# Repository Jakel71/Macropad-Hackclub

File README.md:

# Macropad-Hackclub
This is an Macro pad with 16 Buttons with background lighting. Its meant for simplicity and an everyday use. This is the reason why it will have shortcuts for Windows 11. You could adjust the Container of the PCB so that the lights are looking out, but scince I never saw this kind of LED I don't know how big the hole has to be.

In this picture you can see the Box in gray and the PCB in Green.

Here you can see the shematics of th PCB. It could happen that the Analog pins won't allow Digitalinput, then you schould switsh to an other microcontroller (arduino/ESP) with more pins.

Here you can see the PCB and all the components which you have to mount on it. The dimensions are 137x84.5mm this is more than the limit of 100mm in one dimension, but it would become very messy when you would pack it closer together.

You can see here all the parts you need for the case just screew 4 screews in it and its ready to go.

BOM: (list of materials)
- 1 PCB
- 1 Case ( bittom + top part)
- M3x16mm screws
- M3x5mx4mm heatset inserts
- 16 Cherry MX 1 Keyboardbuttons
- 16 Keycaps
- 16 SK6812 MINI-E LEDs
- 1 Seeed XIAO RP2040

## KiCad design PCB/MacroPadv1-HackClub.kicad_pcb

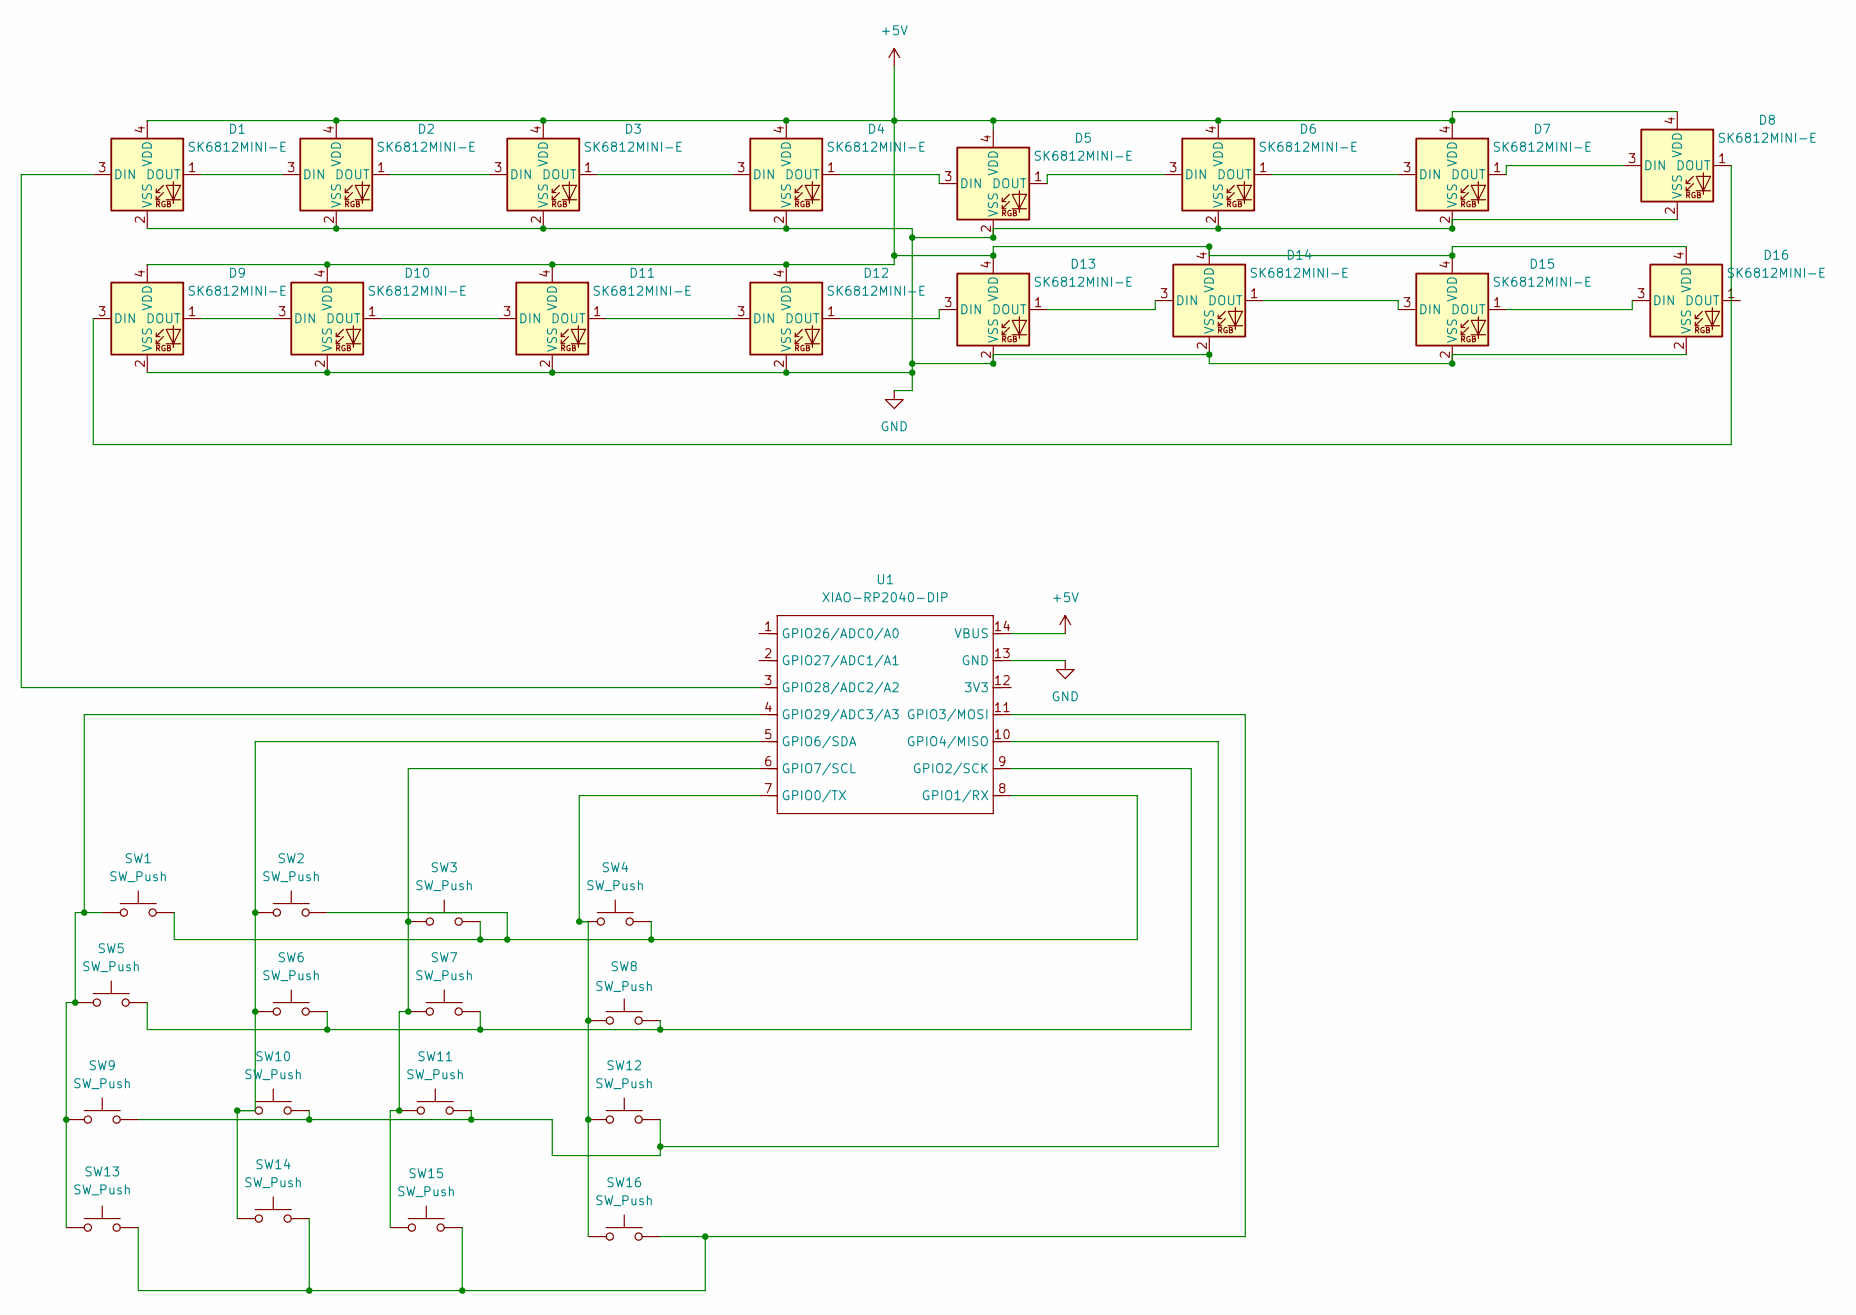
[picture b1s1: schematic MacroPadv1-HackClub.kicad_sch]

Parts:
D1, D2, D3, D4, D5, D6, D7, D8, D9, D10, D11, D12, D13, D14, D15, D16: SK6812MINI-E; MX_SK6812MINI-E
SW1, SW2, SW3, SW4, SW5, SW6, SW7, SW8, SW9, SW10, SW11, SW12, SW13, SW14, SW15, SW16: SW_Push; SW_Cherry_MX_1.00u_PCB
U1: XIAO-RP2040-DIP

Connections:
+5V: D1.4 (VDD), D2.4 (VDD), D3.4 (VDD), D4.4 (VDD), D5.4 (VDD), D6.4 (VDD), D7.4 (VDD), D8.4 (VDD), D9.4 (VDD), D10.4 (VDD), D11.4 (VDD), D12.4 (VDD), D13.4 (VDD), D14.4 (VDD), D15.4 (VDD), D16.4 (VDD), U1.14 (VBUS)
GND: D1.2 (VSS), D2.2 (VSS), D3.2 (VSS), D4.2 (VSS), D5.2 (VSS), D6.2 (VSS), D7.2 (VSS), D8.2 (VSS), D9.2 (VSS), D10.2 (VSS), D11.2 (VSS), D12.2 (VSS), D13.2 (VSS), D14.2 (VSS), D15.2 (VSS), D16.2 (VSS), U1.13 (GND)
unnamed: D1.3 (DIN), U1.3 (GPIO28/ADC2/A2)
unnamed: D1.1 (DOUT), D2.3 (DIN)
unnamed: D2.1 (DOUT), D3.3 (DIN)
unnamed: D3.1 (DOUT), D4.3 (DIN)
unnamed: D4.1 (DOUT), D5.3 (DIN)
unnamed: D5.1 (DOUT), D6.3 (DIN)
unnamed: D6.1 (DOUT), D7.3 (DIN)
unnamed: D7.1 (DOUT), D8.3 (DIN)
unnamed: D8.1 (DOUT), D9.3 (DIN)
unnamed: D9.1 (DOUT), D10.3 (DIN)
unnamed: D10.1 (DOUT), D11.3 (DIN)
unnamed: D11.1 (DOUT), D12.3 (DIN)
unnamed: D12.1 (DOUT), D13.3 (DIN)
unnamed: D13.1 (DOUT), D14.3 (DIN)
unnamed: D14.1 (DOUT), D15.3 (DIN)
unnamed: D15.1 (DOUT), D16.3 (DIN)
unnamed: SW4.1, SW8.1, SW12.1, SW16.1, U1.7 (GPIO0/TX)
unnamed: SW1.2, SW2.2, SW3.2, SW4.2, U1.8 (GPIO1/RX)
unnamed: SW5.2, SW6.2, SW7.2, SW8.2, U1.9 (GPIO2/SCK)
unnamed: SW13.2, SW14.2, SW15.2, SW16.2, U1.11 (GPIO3/MOSI)
unnamed: SW9.2, SW10.2, SW11.2, SW12.2, U1.10 (GPIO4/MISO)
unnamed: SW2.1, SW6.1, SW10.1, SW14.1, U1.5 (GPIO6/SDA)
unnamed: SW3.1, SW7.1, SW11.1, SW15.1, U1.6 (GPIO7/SCL)
unnamed: SW1.1, SW5.1, SW9.1, SW13.1, U1.4 (GPIO29/ADC3/A3)

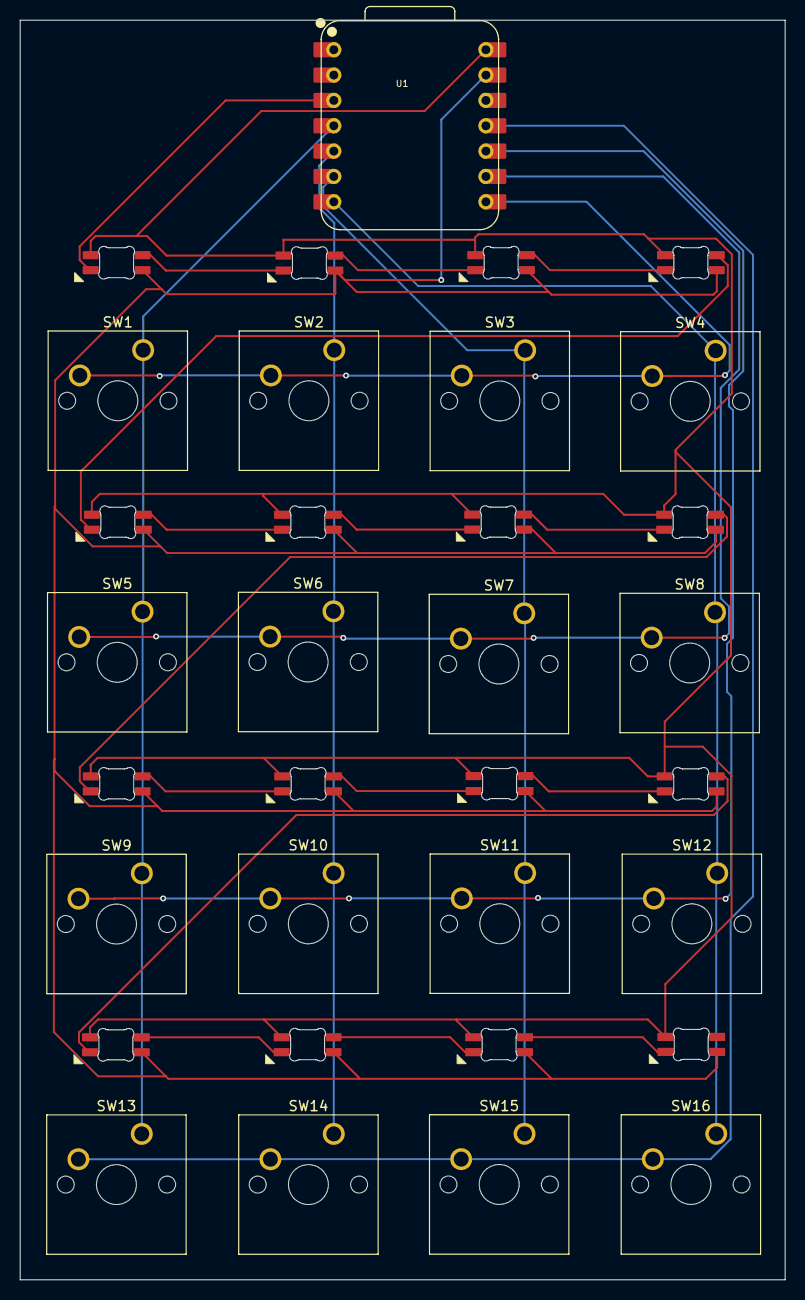
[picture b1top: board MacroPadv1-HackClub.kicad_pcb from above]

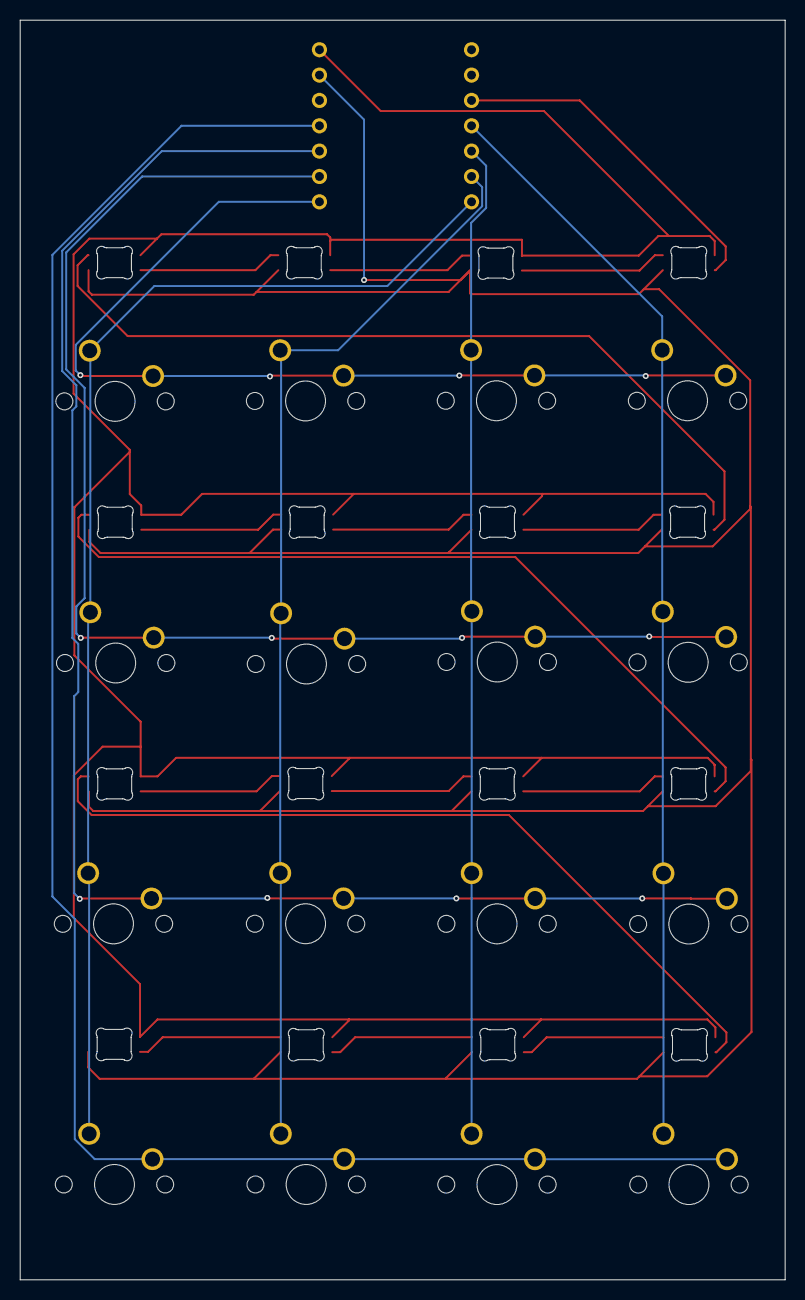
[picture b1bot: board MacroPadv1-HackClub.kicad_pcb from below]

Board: 2 copper layers, 76.6 x 126.2 mm, 33 parts (16 on the bottom side), 26 nets.

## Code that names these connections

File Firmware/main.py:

import board
import digitalio
import time
import usb_hid
from adafruit_hid.keyboard import Keyboard
from adafruit_hid.keycode import Keycode
from adafruit_hid.consumer_control import ConsumerControl
from adafruit_hid.consumer_control_code import ConsumerControlCode
from adafruit_hid.keyboard_layout_us import KeyboardLayoutUS

import neopixel


# -----------------------
# KEYBOARD SETUP
# -----------------------
kbd = Keyboard(usb_hid.devices)
cc = ConsumerControl(usb_hid.devices)
layout = KeyboardLayoutUS(kbd)

# -----------------------
# RGB LED SETUP (16x SK6812 Mini on A2/GPIO28)
# -----------------------
pixel = neopixel.NeoPixel(board.A2, 16, brightness=0.2, auto_write=False)

# All LEDS are red = not ready
for i in range(16):
    pixel[i] = (255, 0, 0)
pixel.show()

# -----------------------
# MATRIX SETUP (4x4)
# -----------------------
# 
# ROWS (right side, Pins 8-11):
#   Pin 8  = GPIO1/RX    = board.RX  oder board.D1
#   Pin 9  = GPIO2/SCK   = board.SCK oder board.D2  
#   Pin 10 = GPIO4/MISO  = board.MISO oder board.D4
#   Pin 11 = GPIO3/MOSI  = board.MOSI oder board.D3
#
# COLUMNS (left side, Pins 4-7):
#   Pin 7 = GPIO0/TX   = board.TX  oder board.D0
#   Pin 6 = GPIO7/SCL  = board.SCL oder board.D7
#   Pin 5 = GPIO6/SDA  = board.SDA oder board.D6
#   Pin 4 = GPIO29/A3  = board.A3
#
# LEDs are on A2 (Pin 3)

row_pins = [board.RX, board.SCK, board.MISO, board.MOSI]  # Pins 8,9,10,11
col_pins = [board.A3, board.SDA, board.SCL, board.TX]     # Pins 4,5,6,7

# Setup Rows as Output (HIGH = deactivated)
rows = []
for pin in row_pins:
    row = digitalio.DigitalInOut(pin)
    row.direction = digitalio.Direction.OUTPUT
    row.value = True  # HIGH = inaktiv
    rows.append(row)

# Setup Columns as Input with Pull-Up
cols = []
for pin in col_pins:
    col = digitalio.DigitalInOut(pin)
    col.direction = digitalio.Direction.INPUT
    col.pull = digitalio.Pull.UP
    cols.append(col)

# -----------------------
# MACRO FUNKTIONS
# -----------------------
def send_macro(keys, modifiers=[]):
    """Sendet eine Tastenkombination"""
    for mod in modifiers:
        kbd.press(mod)
    time.sleep(0.01)
    
    for key in keys:
        kbd.press(key)
        time.sleep(0.01)
        kbd.release(key)
        time.sleep(0.01)
    
    for mod in modifiers:
        kbd.release(mod)

# -----------------------
# KEYMAP DEFINITION
# -----------------------
def key_0():  # Taste 1 // Rickroll
    send_macro([Keycode.R], [Keycode.GUI])  # WIN+R
    time.sleep(0.1)
    layout.write('cmd\n')
    time.sleep(1)
    layout.write('curl ASCII.live&can/zou/hear/me\n')

def key_1():  # Taste 2
    send_macro([Keycode.L], [Keycode.GUI])  # WIN+L // lock screen

def key_2():  # Taste 3
    send_macro([Keycode.F4], [Keycode.ALT])  # ALT+F4 //end current window

def key_3():  # Taste 4
    send_macro([Keycode.D], [Keycode.GUI])  # WIN+D // show desktop

def key_4():  # Taste 5
    send_macro([Keycode.TAB], [Keycode.ALT])  # ALT+TAB // switch window

def key_5():  # Taste 6
    send_macro([Keycode.P], [Keycode.GUI])  # WIN+P // monitor settings

def key_6():  # Taste 7
    send_macro([Keycode.E], [Keycode.GUI])  # WIN+E // open file explorer

def key_7():  # Taste 8
    send_macro([Keycode.LEFT_SHIFT],[Keycode.LEFT_CONTROL], [Keycode.ESCAPE])  # open Taskmanager with STRG+SHIFT+ESC

def key_8():  # Taste 9
    send_macro([Keycode.S], [Keycode.GUI, Keycode.SHIFT])  # WIN+SHIFT+S // Screenshot

def key_9():  # Taste 10
    send_macro([Keycode.I], [Keycode.GUI])  # WIN+I // open settings

def key_10():  # Taste 11
    send_macro([Keycode.K], [Keycode.GUI])  # WIN+K // open connect menu for wireless displays

def key_11():  # Taste 12
    send_macro([Keycode.R], [Keycode.GUI])  # WIN+R // open run dialog

def key_12():  # Taste 13 - Media Play/Pause
    cc.send(ConsumerControlCode.PLAY_PAUSE)

def key_13():  # Taste 14 - Mute
    cc.send(ConsumerControlCode.MUTE)

def key_14():  # Taste 15 - Volume Down
    cc.send(ConsumerControlCode.VOLUME_DECREMENT)

def key_15():  # Taste 16 - Volume Up
    cc.send(ConsumerControlCode.VOLUME_INCREMENT)

# Keymap Array
keymap = [
    [key_0,  key_1,  key_2,  key_3],
    [key_4,  key_5,  key_6,  key_7],
    [key_8,  key_9,  key_10, key_11],
    [key_12, key_13, key_14, key_15]
]

# -----------------------
# LED COLORS
# -----------------------
COLOR_IDLE = (0, 50, 255)      # Blau - Idle
COLOR_PRESSED = (0, 255, 0)    # Grün - Gedrückt

# -----------------------
# DEBOUNCE & STATE
# -----------------------
last_state = [[False for _ in range(4)] for _ in range(4)]
debounce_time = 0.02

# -----------------------
# MAIN LOOP
# -----------------------
print("=== 4x4 Macropad gestartet ===")
print("Rows: RX, SCK, MISO, MOSI (Pins 8-11)")
print("Cols: A3, SDA, SCL, TX (Pins 4,5,6,7)")
print("LEDs: A2 (Pin 3)")

# All LEDS on Blue = ready
for i in range(16):
    pixel[i] = COLOR_IDLE
pixel.show()

while True:
    # Scann Matrix
    for row_idx, row in enumerate(rows):
        # Active Row (LOW = activ)
        row.value = False
        time.sleep(0.005)  # 5ms Debounce
        
        # read Columns
        for col_idx, col in enumerate(cols):
            current_state = not col.value  # inverted for pull-up
            
            # calculate LED Index (left to right)
            led_idx = row_idx * 4 + col_idx
            
            # Check for state change
            if current_state != last_state[row_idx][col_idx]:
                if current_state:  # Taste gedrückt
                    print(f"Taste {led_idx + 1} gedrückt")
                    
                    # LED green
                    pixel[led_idx] = COLOR_PRESSED
                    pixel.show()
                    
                    # do action
                    keymap[row_idx][col_idx]()
                    
                    time.sleep(debounce_time)
                    
                else:  # button no longer pressed
                    # LED back to blue
                    pixel[led_idx] = COLOR_IDLE
                    pixel.show()
                
                last_state[row_idx][col_idx] = current_state
        
        # Deactivate Row (HIGH = inactiv)
        row.value = True
        time.sleep(0.001)  # 1ms Pause between Rows
    
    time.sleep(1)  # 10ms Pause between Scans

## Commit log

2025-12-27 uploading
2025-12-27 Add BOM section with list of materials
    Added a Bill of Materials (BOM) section to the README.
2025-12-27 Revise BOM with detailed component specifications
    Updated BOM with specific hardware components.
2026-01-25 Firmware
2026-01-30 Code+Mini-E
    Added Code and swaped LEDS for the right type
2026-01-31 Update README with images of the Macropad
    Added images to README for better visualization.
2026-01-31 Pcb rerouting
2026-06-06 comments added and redesign on LED startup color and 2 Keys rewritten to be more usefull
